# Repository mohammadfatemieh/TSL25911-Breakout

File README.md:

# TSL25911-Breakout
Breakout with AMS TSL25911 Digital Light Sensor.

* [AMS TSL25911](https://ams.com/TSL25911) Light Sensor
* Detects visible and IR light
* Range: 0.5 lux to 88k lux
* TWI/I2C Interface (address 0x29)
* 3.3V - 5V Power Supply and Logic Level
* Open-Source and released under the [Creative Commons Attribution Share-Alike License](https://creativecommons.org/licenses/by-sa/4.0/).
* **[Documentation on learn.watterott.com](https://learn.watterott.com)**

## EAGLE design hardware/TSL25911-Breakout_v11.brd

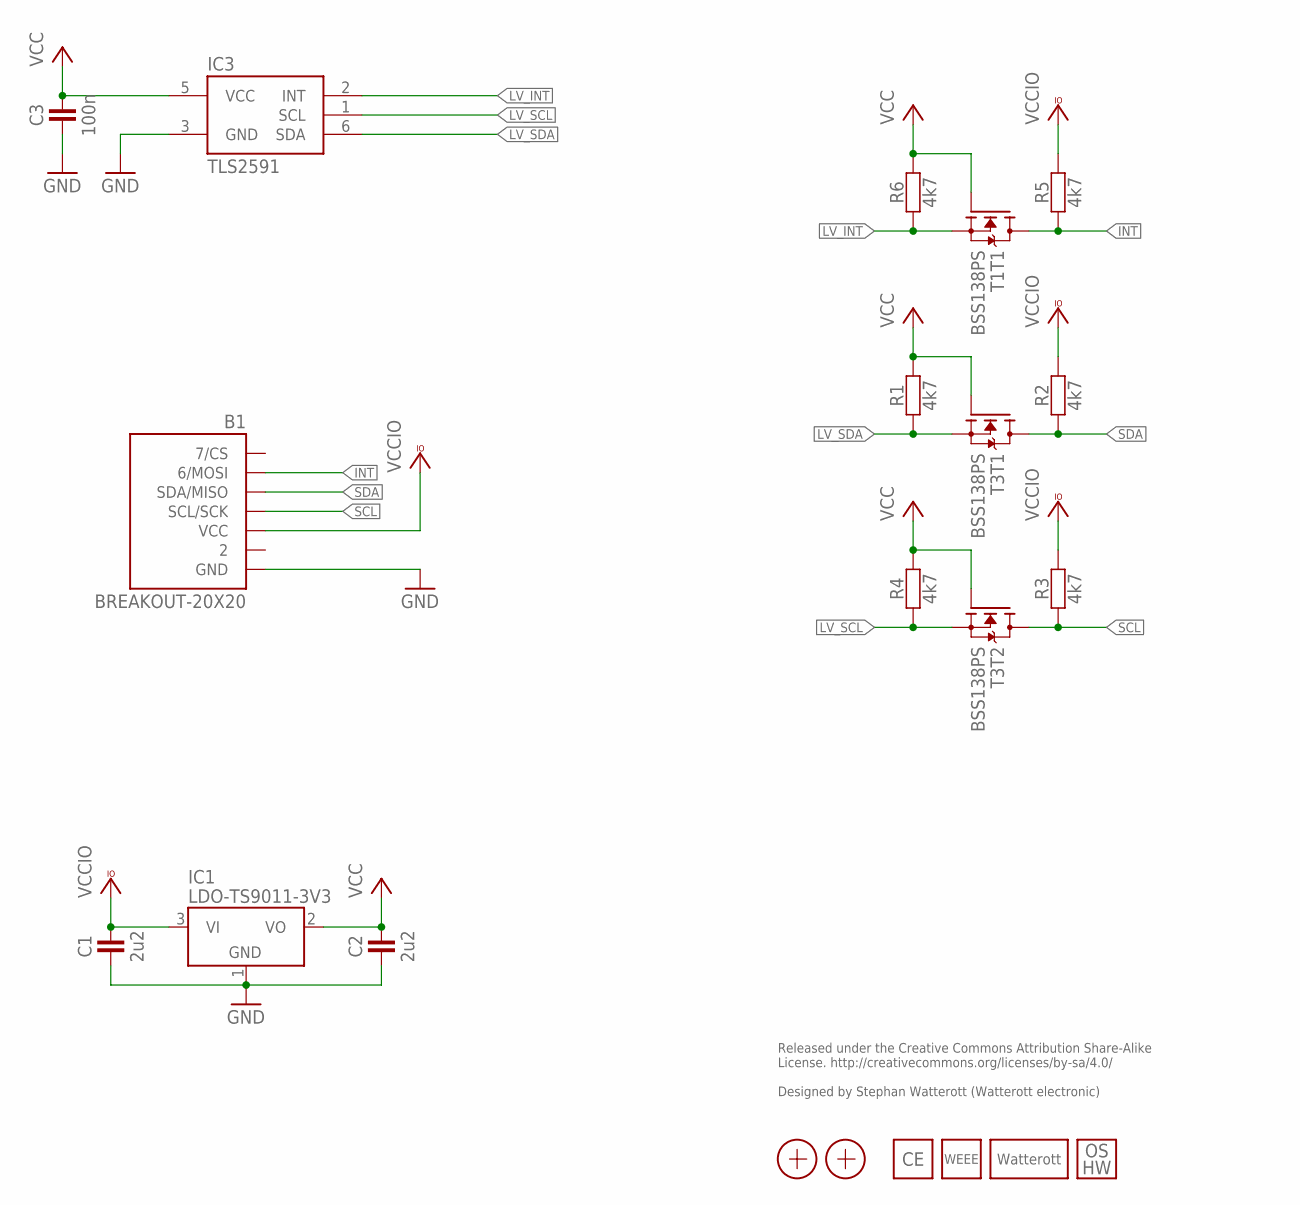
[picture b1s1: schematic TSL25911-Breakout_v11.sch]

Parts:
B1: BREAKOUT-20X20
C1, C2: 2u2; C0402
C3: 100n; C0402
IC1: LDO-TS9011-3V3; SOT23
IC3: TLS2591; WFDFN6
LOGO3: LOGO_WEEE-4; WEEE_4MM
LOGO4: LOGO_CE-4; CE_4MM
LOGO5: LOGO_SPARK-4; SPARK_4MM
LOGO6: LOGO_OSHW-2; OSHW_2MM
R1, R2, R3, R4, R5, R6: 4k7; C0402
T1, T3: BSS138PS; SOT363
X1, X2: PASSER-07; PASSER_07MM

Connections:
GND: B1.GND, C1.1, C2.1, C3.1, IC1.1 (GND), IC3.3 (GND)
INT: B1.MOSI (6/MOSI), R5.1, T1.6 (D)
LV_INT: IC3.2 (INT), R6.1, T1.1 (S)
LV_SCL: IC3.1 (SCL), R4.1, T3.4 (S)
LV_SDA: IC3.6 (SDA), R1.1, T3.1 (S)
SCL: B1.SCL/SCK, R3.1, T3.3 (D)
SDA: B1.SDA/MISO, R2.1, T3.6 (D)
VCC: C2.2, C3.2, IC1.2 (VO), IC3.5 (VCC), R1.2, R4.2, R6.2, T1.2 (G), T3.2 (G), T3.5 (G)
VCCIO: B1.VCC, C1.2, IC1.3 (VI), R2.2, R3.2, R5.2

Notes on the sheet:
Released under the Creative Commons Attribution Share-Alike License. http://creativecommons.org/licenses/by-sa/4.0/ Designed by Stephan Watterott (Watterott electronic)

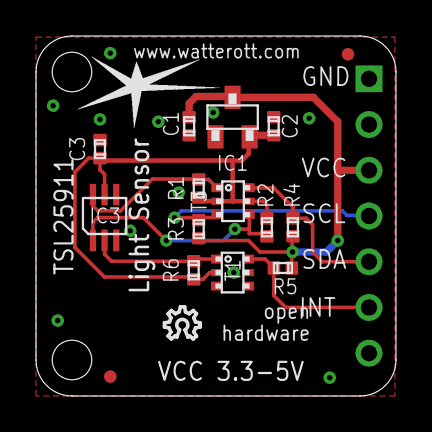
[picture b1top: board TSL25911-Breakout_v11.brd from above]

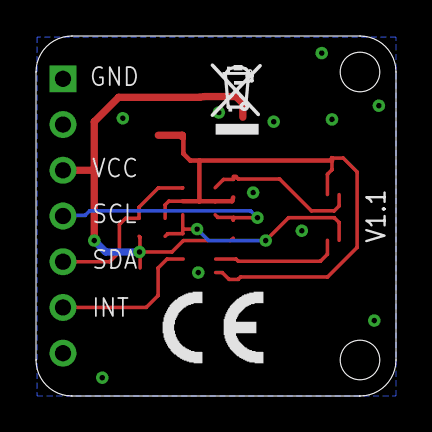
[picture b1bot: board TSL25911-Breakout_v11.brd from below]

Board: 2 copper layers, 20.0 x 20.0 mm, 20 parts (2 on the bottom side), 9 nets.

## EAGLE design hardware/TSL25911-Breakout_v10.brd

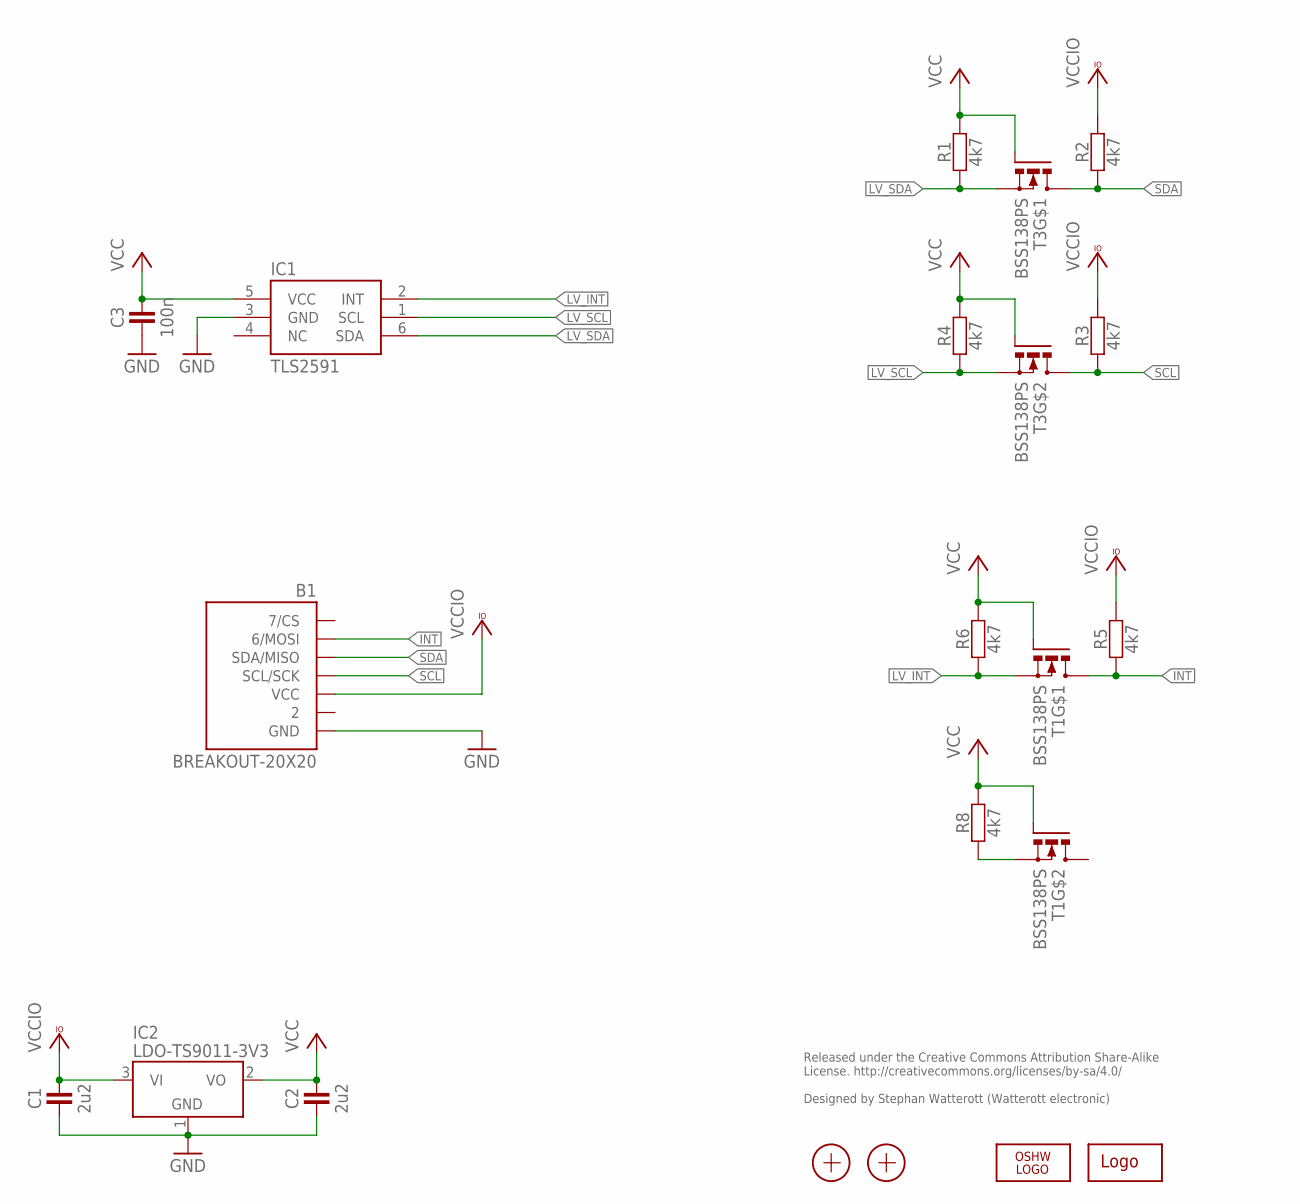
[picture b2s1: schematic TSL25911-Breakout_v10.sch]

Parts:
B1: BREAKOUT-20X20
C1, C2: 2u2; R0402
C3: 100n; R0402
IC1: TLS2591; WFDFN6
IC2: LDO-TS9011-3V3; SOT23
LOGO1: LOGO-S_PLACE_M; SPARK_TPLACE_M
LOGO2: OSHW_LOGOX0070; OSHW_6X70
R1, R2, R3, R4, R5, R6, R8: 4k7; R0402
T1, T3: BSS138PS; SOT363
X1, X2: PASSER-07; PASSER_07MM

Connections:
GND: B1.GND, C1.1, C2.1, C3.1, IC1.3 (GND), IC2.1 (GND)
INT: B1.MOSI (6/MOSI), R5.1, T1.6 (D)
LV_CSB: R8.1, T1.4 (S)
LV_INT: IC1.2 (INT), R6.1, T1.1 (S)
LV_SCL: IC1.1 (SCL), R4.1, T3.4 (S)
LV_SDA: IC1.6 (SDA), R1.1, T3.1 (S)
SCL: B1.SCL/SCK, R3.1, T3.3 (D)
SDA: B1.SDA/MISO, R2.1, T3.6 (D)
VCC: C2.2, C3.2, IC1.5 (VCC), IC2.2 (VO), R1.2, R4.2, R6.2, R8.2, T1.2 (G), T1.5 (G), T3.2 (G), T3.5 (G)
VCCIO: B1.VCC, C1.2, IC2.3 (VI), R2.2, R3.2, R5.2

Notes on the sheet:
Released under the Creative Commons Attribution Share-Alike License. http://creativecommons.org/licenses/by-sa/4.0/ Designed by Stephan Watterott (Watterott electronic)

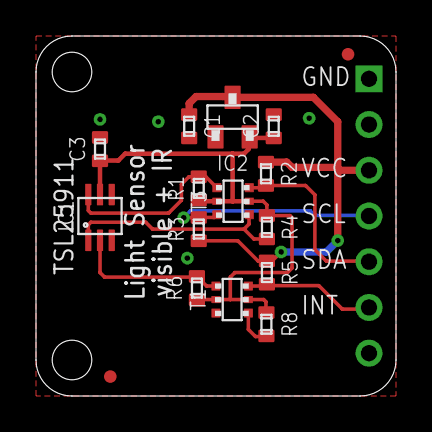
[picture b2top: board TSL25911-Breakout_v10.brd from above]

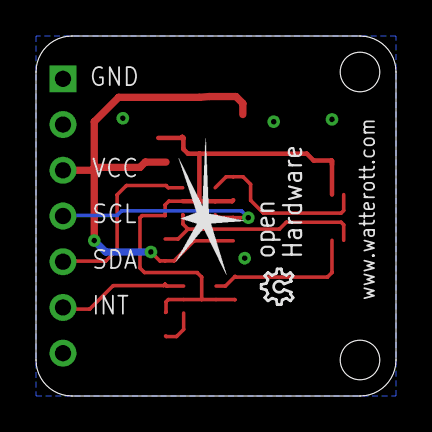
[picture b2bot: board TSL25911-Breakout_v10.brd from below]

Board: 2 copper layers, 20.0 x 20.0 mm, 19 parts (2 on the bottom side), 10 nets.

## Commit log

2019-11-03 added rev 1.1
2019-11-03 updated layout
